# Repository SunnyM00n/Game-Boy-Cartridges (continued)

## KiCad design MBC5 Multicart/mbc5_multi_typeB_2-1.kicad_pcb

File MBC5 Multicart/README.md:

# Game Boy MBC5 Multicart

This is a slightly updated design of my original flashable MBC5-based multicart for the Game Boy. You can make a 2-in-1 or 4-in-1 cartridge, that changes games based on a button press or power cycling the Game Boy. With this board you can also make a single game, but with the addition of a pressable reset button on the cartridge.

**This MBC5 cartridge uses new old stock 29F033 EEPROM chips and battery-backed SRAM.**

The features are as follows:

- Able to make a cartridge with either 2x 2 MB games or 4x 1 MB games
- Adds a pressable button to the cartridge (no shell cutting required)
  - The button can be configured to cycle games on the cart, reset the console, or both
- Configurable to have separate save data for each game, or to share the same save data across multiple games
- Fully compatible with the <a href="https://www.gbxcart.com/">GBxCart RW</a> so you can transfer games and save files to and from the board

Some examples of fun cartridges you can make with this board are:
- A single Pokemon game that has a reset button
- Both Pokemon Red and Blue with separate saves
- Both Pokemon Red and Blue with *the same* save (save files are compatible between versions!)
- Both Pokemon Red and Blue with *the same* save that can switch between versions *during gameplay without resetting* (hotswap!)
- A single copy of Powerpuff Girls with two separate save files

All gerbers and source files can be found in this repo, as this project is fully open source.

## Tutorial Video

This is a video tutorial for the MBC3 multicart specifically, but the process is nearly identical.

")

## Important Things Before You Start

1) To use this board, you need to have an original Game Boy game that uses an MBC5 mapper chip. <a href="https://catskull.net/gb-rom-database/">You can find a list of games and their mappers here</a>. Use the search function. Please note the RAM is in bytes, not bits. Since SRAM in this repo is defined in bits, you need to convert by multiplying the number of bytes by 8.
2) You will need to remove the MBC5 from your donor cartridge for use on this board. This will require a hot air rework station or a hot plate. There's a list below of other parts you can re-use from the donor cartridge.
3) When soldering parts on, it's a good idea to put kapton tape or otherwise cover the bottom cartridge edge. You do not want to get solder on the cartridge contacts.
4) I am not responsible for any damage you do to your self or your property. Attempt this project at your own risk.
5) I do not guarantee design compatibility. You may encounter issues with certain games. There is also a chance I have made an error in the design or the BOM - if this is the case, I will do everything I can to address the problem as quickly as possible.
6) If you are using this board to make games other than for personal use, you must have permission from the originator to use and distribute any ROM images or other related material. You are responsible for making sure you adhere to any license requirements.

DO NOT use my circuit boards for profiting from stolen work - this especially includes homebrew content, ROM hacks, and using fan-made labels without permission from the originator. **Support original creators!**

## Board Characteristics and Order Information

The zipped folder contains all the gerber files for this board. The following options **must** be chosen when ordering boards for yourself.

- Thickness: 0.8mm
- Surface Finish: ENIG
- Gold Fingers: Yes, 30° chamfer

**I sell this blank circuit board on Etsy, so you don't have to buy a bunch of multiples if you don't want to.** (Click the banner!)

You can use the zipped folder at any board fabricator you like. You may also buy the board from PCBWay using this link (disclosure: I receive 10% of the sale value to go twoards future PCB orders of my own):

<a href="https://oshpark.com/shared_projects/IAKoKwEI">The board is also listed on OSH Park as well.</a> **Be sure to get them in 0.8mm thickness if you order from here.**

## Required Equipment

The EEPROM on the board needs to be programmed somehow. There are a few options for doing this:

1) <a href="https://www.gbxcart.com/">**GBxCart**</a>. This is a perfect option if you want an easy way to make Game Boy cartridges without a lot of extra effort. This is a standalone flasher that plugs into your computer via USB. The cartridge circuit board is fully compatible with it, and it makes reflashing games extremely easy using <a href="https://github.com/lesserkuma/FlashGBX">lesserkuma's FlashGBX software</a>.
2) At the lowest level, you can buy an EEPROM programmer with a TSOP chip programming adapter. The downside to this method is that you have to desolder the chip every time you want to program it. The <a href="https://flashcatusb.com/">FlashcatUSB</a> is one popular option in retro spaces, but I use the <a href="https://xgecu.myshopify.com/products/xgecu-new-t48-tl866-3gprogrammer-v12-01-support-28000-ics-for-spi-nor-nand-flash-emmc-bga153-162-169-100-221-tsop-sop-plcc">T48 programmer</a> with the <a href="https://xgecu.myshopify.com/products/100-original-xgecu-adp_f48_ex-1-tsop48-special-adapter-for-nor-flash-only-use-on-t48-tl866-3g-programmer">TSOP48 adapter</a>.

You may also be able to use the <a href="https://github.com/sanni/cartreader">**OSCR**</a> by sanni, but in order to do that you will need to prepare a single ROM file with both games and program it to the first game slot. Or, you will need to add a programming routine into the Arduino code to write a file without erasing the chip first. Consider yourself on your own for this until an addition to the OSCR repository is made to address this.

### How to Program the Cartridges

When using the GBxCart to program multiple games to the cartridge, it's recommended to turn SW2A and SW2B (detailed below) to the OFF position. To change ROM/RAM banks to program, simply press the SW1 tactile button between programming steps. Using FlashGBX's "Refresh" button should show that the game information on the left of the screen changes after pressing the button.

If you're programming the flash chip separate from the board, you'll need to concatenate all the ROM files together into one large 4 MB file to program the chip with.

<a href="https://github.com/MouseBiteLabs/Game-Boy-Cartridges/wiki">Also, you can check out the wiki for more information.</a>

## Battery Safety

When assembling a board, I recommend populating all the parts *except* the battery, and getting it to run initially without it. This is to make it easier to fix any solder connections that might need fixing, without having to worry about getting the battery hot. And if you need to rework anything near the battery after you've put it on the board, be safe and remove it before putting a hot soldering iron next to it.

And this should go without saying, but if you're assembling these boards with a hot plate or hot air, *do not* solder the battery on this way. You should use an iron, and keep heat off of the battery as much as possible. 

(Also check polarity!)

## Board Configurations

There's a lot to cover here. There are four separate switches to configure, and two different sizes of SRAM to pick from.

*Note that you can simply solder bridges from the middle pads of the switches to the left or right to the "ON" or "OFF" positions, instead of installing an actual switch.*

### SRAM Size Selection

There are two sizes of SRAM you can use, and the type you use will dictate how your save data is stored on the cartridge and if it's shared between games or not.

- If you use a 1 Mbit SRAM (like the AS6C1008), then each game you put on the cartridge will have its own separate save files. If you program multiple copies of the same game, then you can effectively have multiple save files on the same cart. Easy example is Pokemon games - they only let you have one save file, but if you put Pokemon Red on the multicart four times, then that gives you four separate save files!
- If you use a 256 Kbit SRAM (like the AS6C62256) then all the games you put on the cartridge will *share* the same RAM space.  This feature is probably only useful for Pokemon games. As an example: this means that if you made a cart that has Pokemon Red and Blue on it, you would play both versions with the same save data, as save data between the two games are compatible with each other.

### Game Cycling Mode Switch (SW2)

SW2, split into two separate switches SW2A (top half) and SW2B (bottom half), controls how you change games on the cartridge. The following table describes the different settings:

| Mode | SW2A (Bottom) | SW2B (Top) | Game change with reset? | Game change with button press? | Does the button reset? |
| ---- | ------------- | ---------- | ----------------------- | ------------------------------ | ---------------------- |
| 1    | OFF           | OFF        | No                      | Yes                            | Yes                    |
| 2    | OFF           | ON         | No                      | Yes                            | No                     |
| 3    | ON            | OFF        | Yes                     | Yes                            | Yes                    |
| 4    | ON            | ON         | Yes                     | No                             | No                     |

*Note: Mode 4 does not give function to the push button at all.*

The "game change" method in this table describes how you advance down the "game" columns described in the table for SW3.

### Game and Save Data Configuration Switch (SW3)

SW3, split into two separate switches SW3A (bottom half) and SW3B (top half), controls the order in which the ROM banks (the games) and the RAM banks (the save data) cycle. This table assumes you are using a 1 Mbit SRAM chip. If you are using a 256 Kbit SRAM, then every entry in the "RAM Banks" column can be described as "1x 256 Kbit", and all the "Game" columns will share that single RAM bank.

Please note that SW3A and SW3B are *different* than the SW3A and SW3B on the MBC3 Multicart PCB.

| Mode | SW3A (Top) | SW3B (Bottom) | ROM Banks  | RAM Banks   | Game 1     | Game 2     | Game 3     | Game 4     |
| ---- | ---- | ---- | ---------- | ----------- | ---------- | ---------- | ---------- | ---------- |
| A    | ON   | OFF  | 2x 2 MB    | 4x 256 Kbit | ROM1, RAM1 | ROM1, RAM2 | ROM2, RAM3 | ROM2, RAM4 |
| B    | OFF  | OFF  | 4x 1 MB    | 4x 256 Kbit | ROM1, RAM1 | ROM2, RAM2 | ROM3, RAM3 | ROM4, RAM4 |
| C    | ON   | ON   | 2x 2 MB    | 2x 256 Kbit | ROM1, RAM1 | ROM2, RAM2 |            |            |
| D    | OFF  | ON   | 2x 1 MB    | 2x 256 Kbit | ROM1, RAM1 | ROM2, RAM2 |            |            |

*Note: Mode D is the same as Mode C, but with restricted space for the ROM, so there's no practical use for Mode D.*

### Game Mode Examples

Here's a list of example cartridges you can make with these settings:
1) Pokemon Red, Blue, Yellow, and Green on one cartridge with separate save files that changes only via pressing the button, which also resets the game: **Mode 1B** with 1 Mbit SRAM
2) Pokemon Red and Blue with separate save files that changes by pressing the button *or* cycling power on the Game Boy: **Mode 3C** with 1 Mbit SRAM
3) Pokemon Red and Blue with the same save file that hotswaps when you press the button on the cartridge (changing games during gameplay): **Mode 2C** with 256 Kbit SRAM

## Test Points and Final Checkout

On the back of the board are five test points. Here's where they are connected:

- TP1: SRAM supply voltage
- TP2: Battery voltage (after R1)
- TP3: Battery voltage (positive terminal of battery)
- TP4: Ground
- TP5: VCC input voltage

After you assemble your game, you should measure the current out of the battery. But first, you should program it with the GBxCart, or if you programmed the EEPROM separately, put it into a Game Boy and cycle power once. Then, flip the PCB upside down on a non-conductive surface (not your leg), and set your multimeter in DC millivolts (or volts). Put the positive probe on TP3 and the negative probe on TP2. If you used a 10kΩ for R1, as indicated in the BOM, you should read a voltage in the single or tens of millivolts. If you have something much higher, especially voltages above 100mV, then you likely have an issue or short circuit on the board somewhere.

**Note: You need to power up the game at least once before battery currents will make sense - the battery management ICs can start up in an unknown state before applying main power to the board.**

To estimate battery life, see <a href="https://github.com/MouseBiteLabs/Game-Boy-MBC5-Cartridge/tree/main/Technical#estimating-battery-life">this section in the Technical Design Document of my first MBC5 design</a>, or for more in-depth analysis, <a href="https://hackaday.io/project/11864-tritiled/log/72554-determining-maximum-runtime-176-to-202-years-cr2032">this Hackaday post</a>.

### Battery Size Considerations

The coin cells commonly used on Game Boy carts in order of increasing size are CR2016, CR2025, and CR2032. The CR2032 is the thickest, but yields the longest battery life.

Batteries that are as large as CR2032 will fit inside the shell, *however*, due to the thickness of the CR2032, using one makes it so the shell cannot be pressed down very easily. This makes the button inside the shell difficult to press reliably. For this reason, I recommend using the CR2025. If you want to use a CR2032 for a bit longer battery life, you should only expect to make a cart that changes games via power cycling only (Modes 3 or 4).

I haven't tested it, but I believe using battery holders instead of pre-tabbed batteries will similarly cause issues with trying to press the button in the middle of the cartridge.

## Board Fitment

The shape of this board was originally meant to mimic original Game Boy circuit boards as closely as possible. Unfortunately, when placed in some aftermarket Game Boy cartridge shells (like those from Cloud Game Store), the circuit board has a lot of freedom to rotate around the main screw hole in the bottom-middle of the cartridge. This can cause misalignment when you put it in a Game Boy, which can cause a game to either not load properly (garbled Game Boy logo) or shut off the Game Boy because of a short circuit. This isn't *dangerous* or anything, just annoying.

In order to make the boards fit nicer in any kind of shell, I added extended tabs of circuit board material to the edges of the cartridges to keep it from rotating too much in shells, which was suggested to me by <a href="https://github.com/orangeglo">orangeglo</a>! (Thanks!)

If you're having trouble fitting the circuit board into a shell, because the tabs interfere with the cart edges, you can safely sand or trim them down as there is no copper within the tabs themselves. The only shell that appears to require any kind of trimming are Kitsch-Bent shells.

## Bill of Materials (BOM)

| Reference Designators | Value/Part Number      | Package        | Description        | Source                                           |
| --------------------- | ---------------------- | -------------- | ------------------ | ------------------------------------------------ |
| B1                    | CR2025, CR2016, CR2032*| See note above | Backup Battery     | [https://mou.sr/3PLccol](https://mou.sr/3PLccol) |
| C1                    | 0.1uF                  | 0603           | Capacitor (MLCC)   | [https://mou.sr/3ENc15O](https://mou.sr/3ENc15O) |
| C4                    | 0.1uF                  | 0603           | Capacitor (MLCC)   | [https://mou.sr/3ENc15O](https://mou.sr/3ENc15O) |
| C5                    | 0.1uF                  | 0603           | Capacitor (MLCC)   | [https://mou.sr/3ENc15O](https://mou.sr/3ENc15O) |
| C6                    | 10uF                   | 0603           | Capacitor (MLCC)   | [https://mou.sr/3mZtSkF](https://mou.sr/3mZtSkF) |
| C7                    | 0.1uF                  | 0603           | Capacitor (MLCC)   | [https://mou.sr/3ENc15O](https://mou.sr/3ENc15O) |
| C8                    | 0.01uF                 | 0603           | Capacitor (MLCC)   | [https://mou.sr/3AsRwK1](https://mou.sr/3AsRwK1) |
| C12                   | 0.1uF                  | 0603           | Capacitor (MLCC)   | [https://mou.sr/3ENc15O](https://mou.sr/3ENc15O) |
| Q1                    | 2N7002                 | SOT-23         | N-Channel FET      | [https://mou.sr/3rgfh6J](https://mou.sr/3rgfh6J) |
| R1                    | 10k                    | 0603           | Resistor           | [https://mou.sr/3riR7IH](https://mou.sr/3riR7IH) |
| R5                    | 130k                   | 0603           | Resistor           | [https://mou.sr/3MjXliy](https://mou.sr/3MjXliy) |
| R6                    | 130k                   | 0603           | Resistor           | [https://mou.sr/3MjXliy](https://mou.sr/3MjXliy) |
| R9                    | 130k                   | 0603           | Resistor           | [https://mou.sr/3MjXliy](https://mou.sr/3MjXliy) |
| R10                   | 49.9k                  | 0603           | Resistor           | [https://mou.sr/3Q3NRZO](https://mou.sr/3Q3NRZO) |
| SW1                   | See note               | 5.2 x 5.2mm    | Tactile Switch     | See Note |
| SW2                   | CAS-D20TA              | J Form Lead    | Dual SPDT          | [https://mou.sr/44YZNT5](https://mou.sr/44YZNT5) |
| SW3                   | CAS-D20TA              | J Form Lead    | Dual SPDT          | [https://mou.sr/44YZNT5](https://mou.sr/44YZNT5) |
| U1                    | 29F032, 29F033         | TSOP-40        | Flash EEPROM       | AliExpress or eBay                               |
| U2                    | MBC5                   | QFP-32         | MBC5 Mapper        | Donor MBC5 Game Boy cartridge                    |
| U3                    | AS6C62256, AS6C1008    | SOP-28, SOP-32 | SRAM               | [https://mou.sr/3sFegFF](https://mou.sr/3sFegFF) |
| U4                    | TPS3613                | MSOP-10        | Battery Management | [https://mou.sr/45Ir2kh](https://mou.sr/45Ir2kh) |
| U5                    | SN74HCS74              | TSSOP-14       | Dual Flip Flop     | [https://mou.sr/3QYGEuT](https://mou.sr/3QYGEuT) |
| U6                    | SN74AHC1G126           | SC70           | Tri-State Buffer   | [https://mou.sr/3T9Zdim](https://mou.sr/3T9Zdim) |
| U7                    | SN74AHC1G126           | SC70           | Tri-State Buffer   | [https://mou.sr/3T9Zdim](https://mou.sr/3T9Zdim) |
| U8                    | SN74AHC1G126           | SC70           | Tri-State Buffer   | [https://mou.sr/3T9Zdim](https://mou.sr/3T9Zdim) |

### Note about SW1

If SW1 is long enough, it will sit inside the shell in a way that lets you press it by lightly pressing on the cartridge shell. This way, you can activate it without removing it from the console. You need to find a switch that has an extended stem on AliExpress, eBay, or Amazon (**if you find a compatible switch on Mouser or Digikey, please let me know**). The measurements will be 5.2 mm x 5.2 mm, with a height of 3.5 mm. Sometimes these parts are listed as "4 mm x 4 mm" or "5 mm x 5 mm" instead. Check the datasheet, if available, to see if it'll fit the footprint. They should have listing pictures similar to the ones seen here:

### Note about SW2, SW3

Instead of using the somewhat pricey switch designated for SW2 and SW3, you can instead just bridge the pads with solder from the middle pad to the pad in the direction you want to set the switch to. For example - in the below picture, SW3A and SW3B are both in the "ON" position in both cases. (Note that the white switches on the right image are switched to the right.)

### Usable Donor Cartridge Parts

You can use a few parts from the donor cart on the new board to save some money. Note that you will generally get better reliability with new parts as opposed to old ones. For example: I have seen failed RAM chips from donors in the past.

1) **U2: MBC5** - This one is required
2) **U3: SRAM** - You can use this part *only if* the sum of the RAM space for the games you're using is the same or less amount of RAM that the donor cartridge has. If you plan to have separate save data for every game, you'll probably need to buy an AS6C1008.

You could probably transfer over most of the 0.1uF capacitors but they're pretty cheap anyway, so I generally just recommend buying new resistors and capacitors.

## Things to Remember

- The 29F032 and 29F033 have been known to occasionally be defective upon arrival. They're either used, or new old stock, and usually only available from AliExpress.
- The footprint for the battery can fit a CR2032, CR2025, or CR2016 with solder tabs. The only difference is the mAh capacity (larger number = longer life). If you get Panasonic tabbed batteries, you may have to trim the battery tabs to make them fit on the footprint.
- Generally, ROM sizes are conveyed in terms of kilobytes and megabytes (KB, MB). RAM size is usually conveyed in terms of kilobits or megabits (Kbit, Mbit). You can convert Kbit and Mbit to KB and MB by dividing Kbit or Mbit by 8. For example, 256 Kbit = 32 KB.

## Labels

If you want a Bucket Mouse branded label for your cartridge, look no further than <a href="https://krizdingus.com/mousebitelabs/">krizdingus's designs</a>. Special thanks to Kris for designing these, they look awesome! (If you are going to order/print these, use the high-res images hosted on his website, and *keep the labels for personal or non-commercial use only.*)

## Why not FRAM?

This particular board is designed for using low retention power SRAM, or Static RAM. One downside to SRAM is that you need a battery to keep the SRAM powered on even when the game is turned off if you want to retain the data on the chip. So eventually the battery will die, and your save data will be lost.

The other popular option for holding save data is using FRAM, or Ferroelectric RAM, to keep save data around even after the battery dies (specifically, the popular part that's used for Game Boy FRAM carts is the FM18W08).

So, why would anyone ever use SRAM over FRAM if FRAM doesn't need a battery? Well, they do come with a number of downsides:

1) Quality, new stock, 5V tolerant FRAM is expensive ($12+ per part).
2) Cheaper FRAM chips from eBay or Aliexpress are notoriously flaky (anecdotally, ~50% success rate).
3) **FM18W08 maxes out at 256K (which is restrictive for multicarts).**
4) FRAM memory access requires different chip select timing than SRAM, and the Game Boy expects SRAM, so it is not natively compatible with FRAM carts. The Gameboy Color specifically cannot (easily) be made to properly access FM18W08 chip. You *can* use an OR gate and add the CLK on the cart edge to try to achieve the necessary timing, but it only works (properly) for DMG/MGB/SGB, not the GBC. It usually *works* in practice for GBC, but it's technically a datasheet violation and can potentially cause issues in edge cases. <a href="https://github.com/Gekkio">(Thanks to gekkio for pointing this out!)</a>

In contrast, *brand new* quality SRAM chips are ~$3, and you can even save that by using the original SRAM from a donor cartridge if you want to. You will easily get more than a decade of life running on a battery. You're already assembling this cartridge; you can dump the save and replace the battery before then.

## Revision History

### v2.1
- Removed triangle on silkscreen from U8

### v2.0
- Fixed issue with previous design where SW2A being in the ON position caused excess save battery drain
- Added board number to the top of the board
- Updated silkscreen and cartridge style to match my other Game Boy cartridges
- Removed R8, made EEPROM writable via the /WR pin on the cart edge

### v1.3
- Fixed debounce circuit for push button
- Adjusted board edge tabs to better fit in shells

### v1.2
- Added nubs on the board edge to prevent the circuit board from rattling around in aftermarket cartridges

### v1.1
- Fix schematic errors
- Extended cart edge down by 0.25 mm for better fitment
- Added OSHW logo and "SUPPORT ORIGINAL CREATORS!"

### v1.0
- Prototype revision

## Resources and Acknowledgements

- <a href="http://www.devrs.com/gb/files/hardware.html">Jeff Frohwein's GameBoy Tech Page</a>
- <a href="https://gbhwdb.gekkio.fi/">Game Boy Hardware Database</a>
- <a href="https://catskull.net/gb-rom-database/">Nintendo Gameboy Game List</a>
- <a href="https://www.gbxcart.com/">insideGadgets discord server for GBxCart RW compatibility requirements</a>
- <a href="https://github.com/lesserkuma/FlashGBX">Lesserkuma's FlashGBX software</a>
- <a href="https://www.ti.com/lit/ds/symlink/tps3613-01.pdf?HQS=dis-mous-null-mousermode-dsf-pf-null-wwe&ts=1698238885366&ref_url=https%253A%252F%252Feu.mouser.com%252F">TPS3613 Datasheet</a>
- Board outline modified from <a href="https://tinkerer.us/projects/homebrew-gameboy-cartridge.html">Dillon Nichols's Homebrew Gameboy Cartridge project</a>
- Thanks to <a href="https://github.com/orangeglo">orangeglo</a> for his suggestion of adding spacers around the board edge for better fitment in aftermarket cartridges
- Some components from <a href="https://github.com/adafruit/Adafruit-Eagle-Library">Adafruit's Eagle parts library</a>
- Some components from <a href="https://www.snapeda.com/">SnapMagic</a>
- Thank you to <a href="https://github.com/Gekkio">gekkio</a> for their deep Game Boy knowledge resources, and for collaboration in demystifying some of the design choices on Game Boy cartridges

## License

<br />This work is licensed under a <a rel="license" href="http://creativecommons.org/licenses/by-sa/4.0/">Creative Commons Attribution-ShareAlike 4.0 International License</a>. You are able to copy and redistribute the material in any medium or format, as well as remix, transform, or build upon the material for any purpose (even commercial) - but you **must** give appropriate credit, provide a link to the license, and indicate if any changes were made.

©MouseBiteLabs 2025

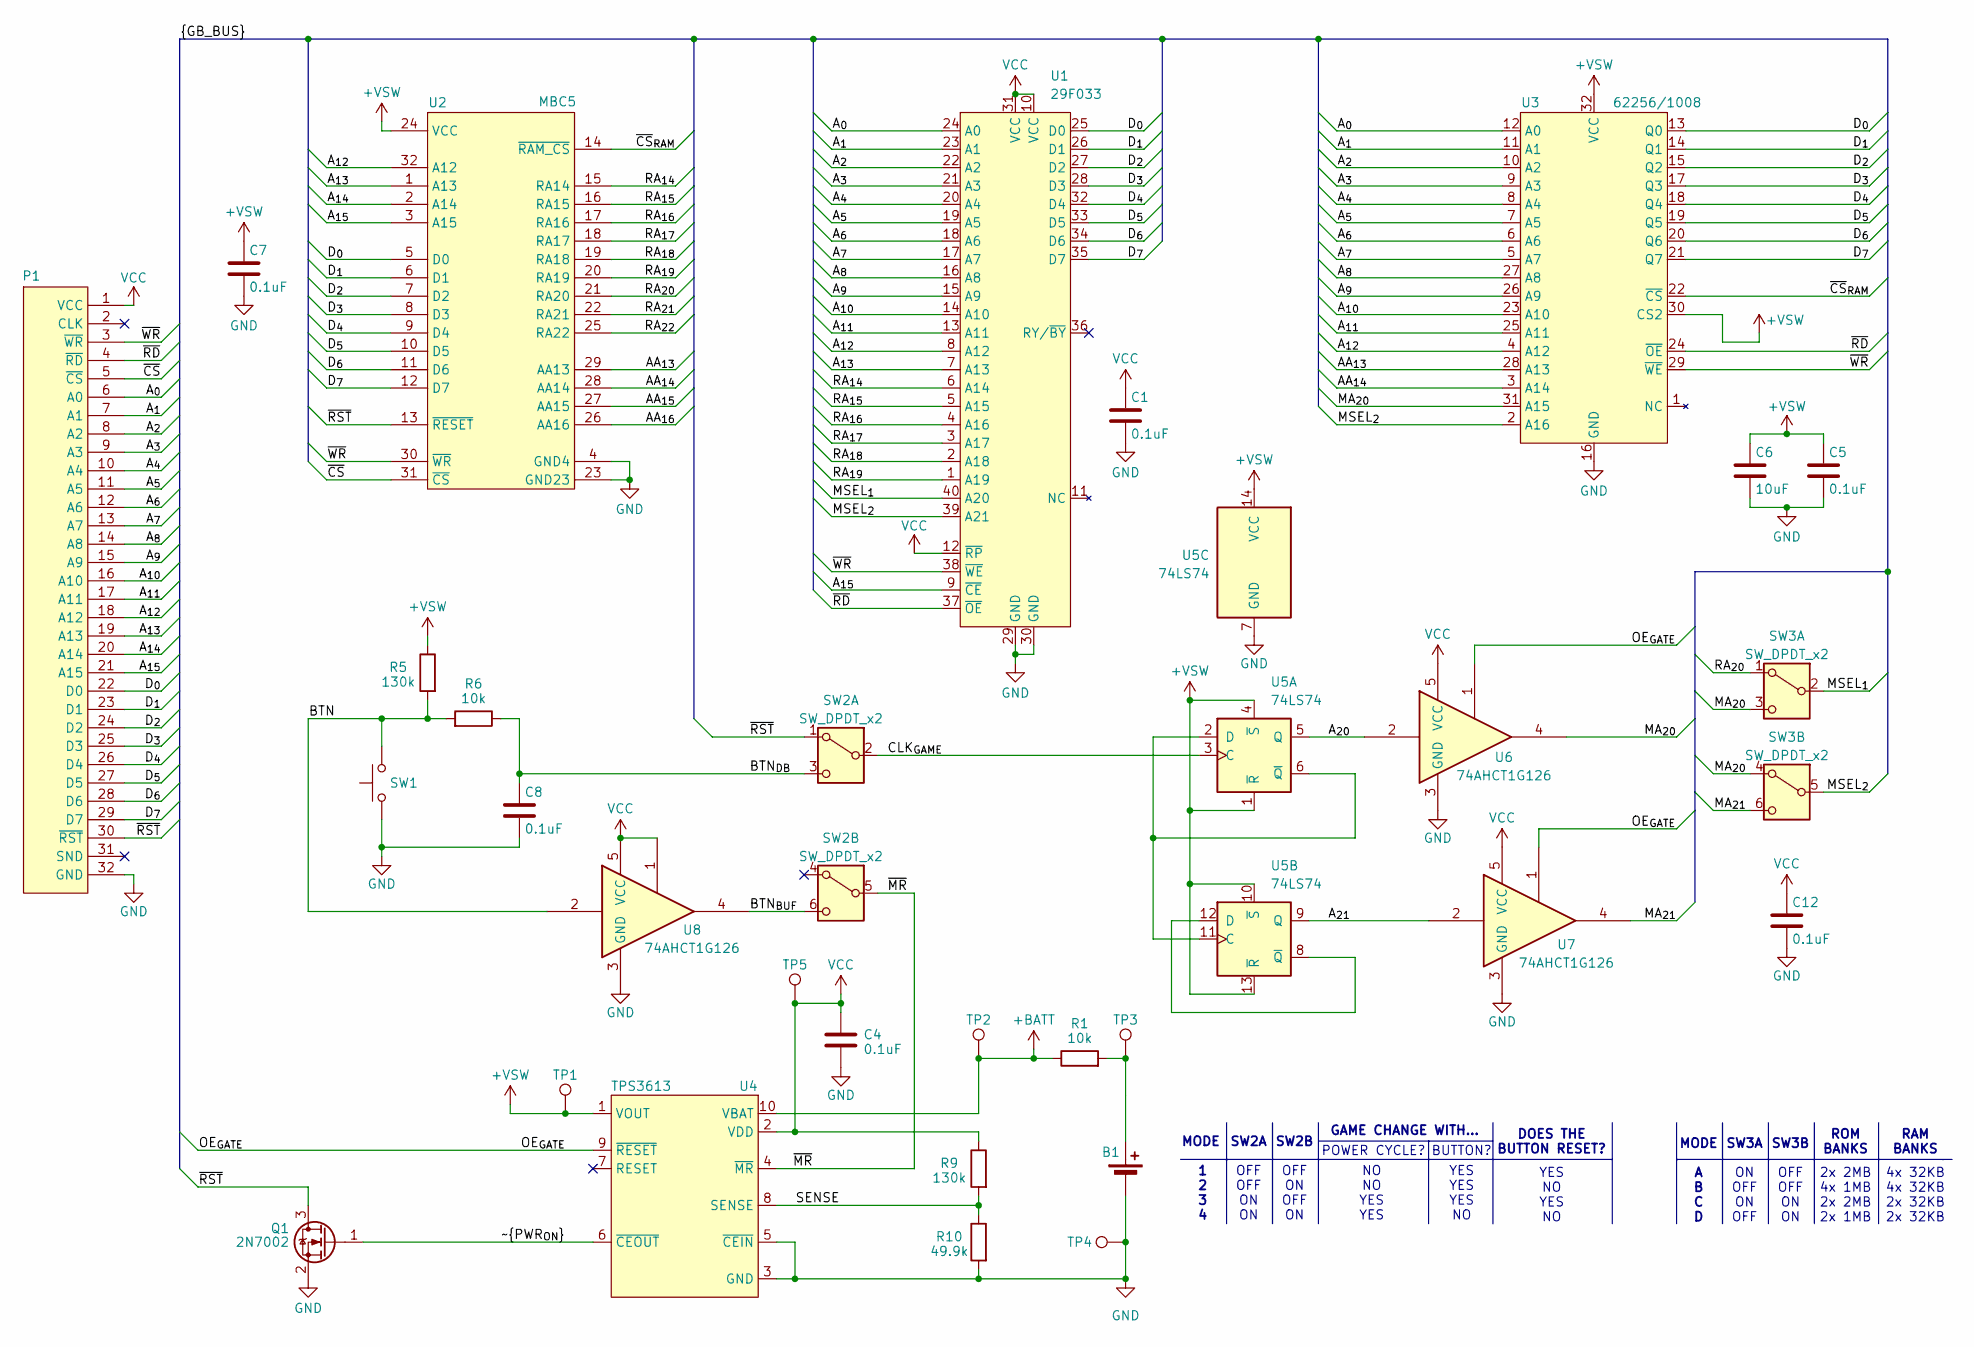
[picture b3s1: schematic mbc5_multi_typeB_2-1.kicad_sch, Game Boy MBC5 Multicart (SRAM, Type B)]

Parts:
B1: CR2025
C1, C4, C5, C7, C8, C12: 0.1uF; C_0603_1608Metric_Boxed
C6: 10uF; C_0603_1608Metric_Boxed
P1: GBC_CARTTAB; GBC_CART_TABBED
Q1: 2N7002; SOT-23
R1, R6: 10k; R_0603_1608Metric_Boxed
R5, R9: 130k; R_0603_1608Metric_Boxed
R10: 49.9k; R_0603_1608Metric_Boxed
SW1: SW_SPST_Momentary; Pushbutton
SW2, SW3: SW_DPDT_x2; CAS-D20A
TP1, TP2, TP3, TP4, TP5: TPB1,27; TestPoint_Pad_D1.0mm
U1: 29F033; TSOP-I-40_18.4x12mm_P0.5mm_1
U2: MBC5; QFP-32
U3: 62256/1008; SO32L_L
U4: TPS3613; MSOP-10_3x3mm_P0.5mm
U5: 74LS74; TSSOP-14_4.4x5mm_P0.65mm
U6, U7, U8: 74AHCT1G126; SOT-353_SC-70-5

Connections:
+BATT: R1.1, TP2.1, U4.10 (VBAT)
+VSW: C5.1, C6.1, C7.1, R5.1, TP1.1, U2.24 (VCC), U3.30 (CS2), U3.32 (VCC), U4.1 (VOUT), U5.1 (~R), U5.4 (~S), U5.10 (~S), U5.13 (~R), U5.14 (VCC)
/AA_{13}: U2.29 (AA13), U3.28 (A13)
/AA_{14}: U2.28 (AA14), U3.3 (A14)
/AA_{15}: U2.27 (AA15)
/AA_{16}: U2.26 (AA16)
/A_{0}: P1.6 (A0), U1.24 (A0), U3.12 (A0)
/A_{1}: P1.7 (A1), U1.23 (A1), U3.11 (A1)
/A_{2}: P1.8 (A2), U1.22 (A2), U3.10 (A2)
/A_{3}: P1.9 (A3), U1.21 (A3), U3.9 (A3)
/A_{4}: P1.10 (A4), U1.20 (A4), U3.8 (A4)
/A_{5}: P1.11 (A5), U1.19 (A5), U3.7 (A5)
/A_{6}: P1.12 (A6), U1.18 (A6), U3.6 (A6)
/A_{7}: P1.13 (A7), U1.17 (A7), U3.5 (A7)
/A_{8}: P1.14 (A8), U1.16 (A8), U3.27 (A8)
/A_{9}: P1.15 (A9), U1.15 (A9), U3.26 (A9)
/A_{10}: P1.16 (A10), U1.14 (A10), U3.23 (A10)
/A_{11}: P1.17 (A11), U1.13 (A11), U3.25 (A11)
/A_{12}: P1.18 (A12), U1.8 (A12), U2.32 (A12), U3.4 (A12)
/A_{13}: P1.19 (A13), U1.7 (A13), U2.1 (A13)
/A_{14}: P1.20 (A14), U2.2 (A14)
/A_{15}: P1.21 (A15), U1.9 (~CE), U2.3 (A15)
/A_{20}: U5.5 (Q), U6.2
/A_{21}: U5.9 (Q), U7.2
/BTN: R5.2, R6.2, SW1.2, U8.2
/BTN_{BUF}: SW2.6 (C), U8.4
/BTN_{DB}: C8.1, R6.1, SW2.3 (C)
/CLK_{GAME}: SW2.2 (B), U5.3 (C)
/D_{0}: P1.22 (D0), U1.25 (D0), U2.5 (D0), U3.13 (Q0)
/D_{1}: P1.23 (D1), U1.26 (D1), U2.6 (D1), U3.14 (Q1)
/D_{2}: P1.24 (D2), U1.27 (D2), U2.7 (D2), U3.15 (Q2)
/D_{3}: P1.25 (D3), U1.28 (D3), U2.8 (D3), U3.17 (Q3)
/D_{4}: P1.26 (D4), U1.32 (D4), U2.9 (D4), U3.18 (Q4)
/D_{5}: P1.27 (D5), U1.33 (D5), U2.10 (D5), U3.19 (Q5)
/D_{6}: P1.28 (D6), U1.34 (D6), U2.11 (D6), U3.20 (Q6)
/D_{7}: P1.29 (D7), U1.35 (D7), U2.12 (D7), U3.21 (Q7)
/MA_{20}: SW3.3 (C), SW3.4 (A), U3.31 (A15), U6.4
/MA_{21}: SW3.6 (C), U7.4
/MSEL_{1}: SW3.2 (B), U1.40 (A20)
/MSEL_{2}: SW3.5 (B), U1.39 (A21), U3.2 (A16)
/OE_{GATE}: U4.9 (~RESET), U6.1, U7.1
/RA_{14}: U1.6 (A14), U2.15 (RA14)
/RA_{15}: U1.5 (A15), U2.16 (RA15)
/RA_{16}: U1.4 (A16), U2.17 (RA16)
/RA_{17}: U1.3 (A17), U2.18 (RA17)
/RA_{18}: U1.2 (A18), U2.19 (RA18)
/RA_{19}: U1.1 (A19), U2.20 (RA19)
/RA_{20}: SW3.1 (A), U2.21 (RA20)
/RA_{21}: U2.22 (RA21)
/RA_{22}: U2.25 (RA22)
/SENSE: R9.2, R10.1, U4.8 (SENSE)
/~CS: P1.5 (~CS), U2.31 (~CS)
/~CS_{RAM}: U2.14 (~RAM_CS), U3.22 (~CS)
/~MR: SW2.5 (B), U4.4 (~MR)
/~PWR_{ON}: Q1.1 (G), U4.6 (~CEOUT)
/~RD: P1.4 (~RD), U1.37 (~OE), U3.24 (~OE)
/~RST: P1.30 (~RST), Q1.3 (D), SW2.1 (A), U2.13 (~RESET)
/~WR: P1.3 (~WR), U1.38 (~WE), U2.30 (~WR), U3.29 (~WE)
GND: B1.2 (-), C1.2, C4.2, C5.2, C6.2, C7.2, C8.2, C12.2, P1.32 (GND), Q1.2 (S), R10.2, SW1.1, TP4.1, U1.29 (GND), U1.30 (GND), U2.4 (GND4), U2.23 (GND23), U3.16 (GND), U4.3 (GND), U4.5 (~CEIN), U5.7 (GND), U6.3 (GND), U7.3 (GND), U8.3 (GND)
unnamed: B1.1 (+), R1.2, TP3.1
unnamed: U5.2 (D), U5.6 (~Q), U5.11 (C)
unnamed: U5.8 (~Q), U5.12 (D)
VCC: C1.1, C4.1, C12.1, P1.1 (VCC), R9.1, TP5.1, U1.10 (VCC), U1.12 (~RP), U1.31 (VCC), U4.2 (VDD), U6.5 (VCC), U7.5 (VCC), U8.1, U8.5 (VCC)

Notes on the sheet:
RAM BANKS
BUTTON?
A B C D
YES NO YES NO
SW2A
SW3B
OFF OFF ON ON
MODE
OFF ON OFF ON
DOES THE BUTTON RESET?
YES YES YES NO
1 2 3 4
4x 32KB 4x 32KB 2x 32KB 2x 32KB
ROM BANKS
SW3A
POWER CYCLE?
NO NO YES YES
SW2B
2x 2MB 4x 1MB 2x 2MB 2x 1MB
GAME CHANGE WITH...
ON OFF ON OFF

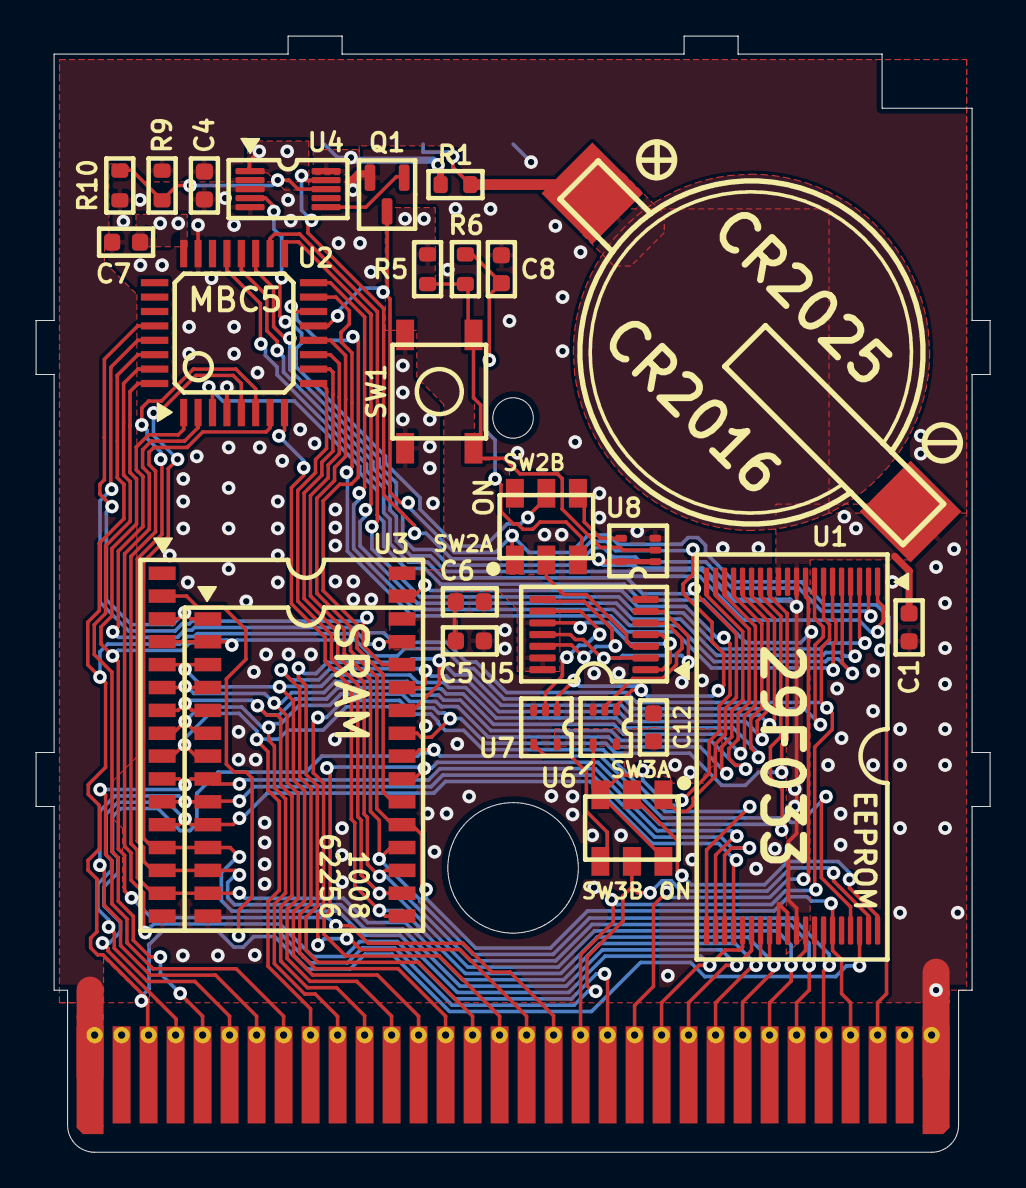
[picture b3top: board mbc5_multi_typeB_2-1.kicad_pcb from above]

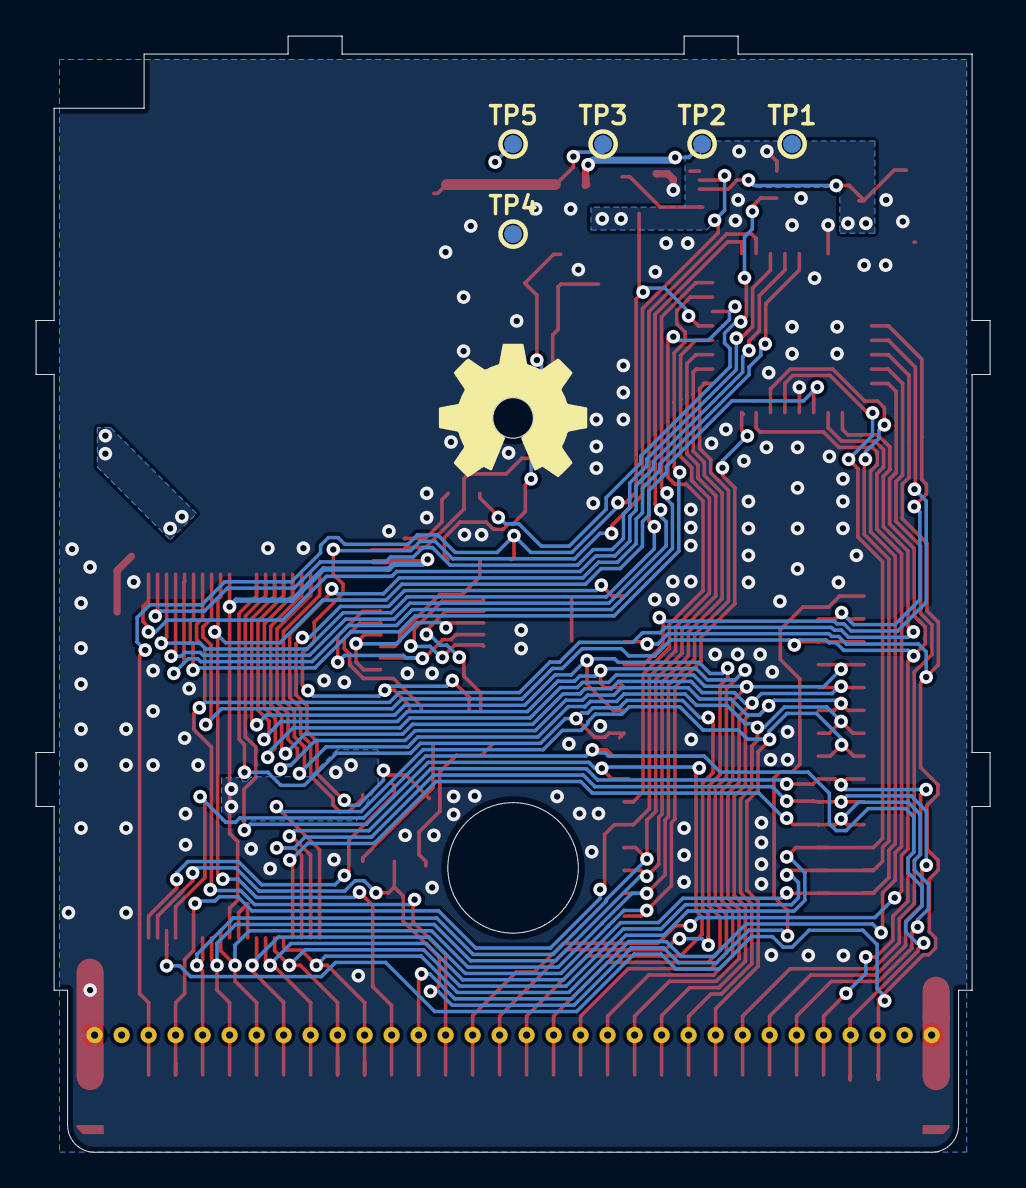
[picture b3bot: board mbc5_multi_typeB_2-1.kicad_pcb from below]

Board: 2 copper layers, 53.0 x 62.0 mm, 31 parts (5 on the bottom side), 59 nets.

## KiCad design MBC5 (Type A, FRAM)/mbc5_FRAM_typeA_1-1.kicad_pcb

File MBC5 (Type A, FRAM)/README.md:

# Game Boy MBC5 Cartridge - Type A, FRAM

This is an alternate design of my <a href="https://github.com/MouseBiteLabs/Game-Boy-Cartridges/tree/main/MBC5%20(Type%20A%2C%20SRAM)">flashable MBC5-based cartridge for the Game Boy</a>. This board uses non-volatile FRAM instead of SRAM to hold save data. I made this specifically for use with the <a href="https://github.com/MouseBiteLabs/Super-Game-Boy-Plus/tree/main">Super Game Boy Plus boards.</a>

**This MBC5 cartridge uses brand new M29F160 EEPROM chips and non-volatile FRAM.**

This circuit board should cover most MBC5 games, and is able to make games up to 2 MB in size, that use up to 256 Kbit of RAM. It is fully compatible with both the <a href="https://www.gbxcart.com/">GBxCart RW</a> and sanni's <a href="https://github.com/sanni/cartreader">Open Source Cart Reader (OSCR)</a> so you can transfer games and save files to and from the board. Because of the FRAM this board utilizes, <a href="https://github.com/MouseBiteLabs/Game-Boy-Cartridges/tree/main/MBC5%20(Type%20A%2C%20SRAM)#why-not-fram">it is technically only fully compatible with regular Game Boy games, and not Game Boy Color games,</a> though no issues have been reported in the past when using them with Game Boy Color games.

All gerbers and source files can be found in this repo, as this project is fully open source.

## Important Things Before You Start

1) To use this board, you need to have an original Game Boy game that uses an MBC5 mapper chip. <a href="https://catskull.net/gb-rom-database/">You can find a list of games and their mappers here</a>. Use the search function. Please note the RAM is in bytes, not bits. Since RAM in this repo is defined in bits, you need to convert by multiplying the number of bytes by 8.
2) You will need to remove the MBC5 from your donor cartridge for use on this board. This will require a hot air rework station or a hot plate. There's a list below of other parts you can re-use from the donor cartridge.
3) When soldering parts on, it's a good idea to put kapton tape or otherwise cover the bottom cartridge edge. You do not want to get solder on the cartridge contacts.
4) I am not responsible for any damage you do to your self or your property. Attempt this project at your own risk.
5) I do not guarantee design compatibility. You may encounter issues with certain games. There is also a chance I have made an error in the design or the BOM - if this is the case, I will do everything I can to address the problem as quickly as possible.
6) If you are using this board to make games other than for personal use, you must have permission from the originator to use and distribute any ROM images or other related material. You are responsible for making sure you adhere to any license requirements.

DO NOT use my circuit boards for profiting from stolen work - this especially includes homebrew content, ROM hacks, and using fan-made labels without permission from the originator. **Support original creators!**

## Board Characteristics and Order Information

The zipped folder contains all the gerber files for this board. The following options **must** be chosen when ordering boards for yourself.

- Thickness: 0.8mm
- Surface Finish: ENIG
- Gold Fingers: Yes, 30° chamfer

**I sell this blank circuit board on Etsy, so you don't have to buy a bunch of multiples if you don't want to.** (Click the banner!)

(Not yet available - this is a placeholder.)

You can use the zipped folder at any board fabricator you like. You may also buy the board from PCBWay using this link (disclosure: I receive 10% of the sale value to go towards future PCB orders of my own):

<a href="https://oshpark.com/shared_projects/4iVMHuUe">The board is also listed on OSH Park as well.</a> **Be sure to get them in 0.8mm thickness if you order from here.**

## Required Equipment

The EEPROM on the board needs to be programmed somehow. There are a few options for doing this:

1) <a href="https://www.gbxcart.com/">**GBxCart**</a>. This is a perfect option if you want an easy way to make Game Boy cartridges without a lot of extra effort. This is a standalone flasher that plugs into your computer via USB. The cartridge circuit board is fully compatible with it, and it makes reflashing games extremely easy using <a href="https://github.com/lesserkuma/FlashGBX">lesserkuma's FlashGBX software</a>.
2) <a href="https://github.com/sanni/cartreader">**OSCR**</a> by sanni. This is the Open Source Cart Reader, capable of making backups of both the ROM and RAM contents of cartridges across many different systems - like the NES, SNES, Genesis, and of course Game Boy and Game Boy Advance. And you can also use it to flash these Game Boy cartridges. The OSCR however requires assembly (or someone to assemble it for you) and is a bit more cumbersome to interface with on a PC, but it's an extremely powerful tool that I can't recommend enough if you want to expand past Game Boys.
3) At the lowest level, you can buy an EEPROM programmer with a TSOP chip programming adapter. The downside to this method is that you have to desolder the chip every time you want to program it. The <a href="https://flashcatusb.com/">FlashcatUSB</a> is one popular option in retro spaces, but I use the <a href="https://xgecu.myshopify.com/products/xgecu-new-t48-tl866-3gprogrammer-v12-01-support-28000-ics-for-spi-nor-nand-flash-emmc-bga153-162-169-100-221-tsop-sop-plcc">T48 programmer</a> with the <a href="https://xgecu.myshopify.com/products/100-original-xgecu-adp_f48_ex-1-tsop48-special-adapter-for-nor-flash-only-use-on-t48-tl866-3g-programmer">TSOP48 adapter</a>.

### How to Program the Cartridges

<a href="https://github.com/MouseBiteLabs/Game-Boy-Cartridges/wiki">Check out the wiki for more information.</a>

## Board Fitment

The shape of this board was originally meant to mimic original Game Boy circuit boards as closely as possible. Unfortunately, when placed in some aftermarket Game Boy cartridge shells (like those from Cloud Game Store), the circuit board has a lot of freedom to rotate around the main screw hole in the bottom-middle of the cartridge. This can cause misalignment when you put it in a Game Boy, which can cause a game to either not load properly (garbled Game Boy logo) or shut off the Game Boy because of a short circuit. This isn't *dangerous* or anything, just annoying.

In order to make the boards fit nicer in any kind of shell, I added extended tabs of circuit board material to the edges of the cartridges to keep it from rotating too much in shells, which was suggested to me by <a href="https://github.com/orangeglo">orangeglo</a>! (Thanks!)

If you're having trouble fitting the circuit board into a shell, because the tabs interfere with the cart edges, you can safely sand or trim them down as there is no copper within the tabs themselves. The only shell that appears to require any kind of trimming are Kitsch-Bent shells.

## Bill of Materials (BOM)

| Reference | Value/Part Number | Package | Description      | Source                                           |
| --------- | ----------------- | ------- | ---------------- | ------------------------------------------------ |
| C19       | 0.1u              | 0603    | Capacitor (MLCC) | [https://mou.sr/3ENc15O](https://mou.sr/3ENc15O) |
| C20       | 0.1u              | 0603    | Capacitor (MLCC) | [https://mou.sr/3ENc15O](https://mou.sr/3ENc15O) |
| C21       | 0.1u              | 0603    | Capacitor (MLCC) | [https://mou.sr/3ENc15O](https://mou.sr/3ENc15O) |
| C22       | 0.1u              | 0603    | Capacitor (MLCC) | [https://mou.sr/3ENc15O](https://mou.sr/3ENc15O) |
| R17       | 10k               | 0603    | Resistor         | [https://mou.sr/3riR7IH](https://mou.sr/3riR7IH) |
| U7        | M29F160           | TSOP-48 | Flash EEPROM     | [https://mou.sr/3MNWQ0b](https://mou.sr/3MNWQ0b) |
| U8        | MBC5              | QFP-32  | MBC5 Mapper      | Donor Game Boy Game                              |
| U9        | FM18W08-SG        | SOIC-28 | FRAM             | [https://mou.sr/4cRIJlb](https://mou.sr/4cRIJlb) |
| U10       | SN74LVC1G332      | SOT-363 | 3-input Or Gate  | [https://mou.sr/3XdbXoN](https://mou.sr/3XdbXoN) |

## Labels

If you want a Bucket Mouse branded label for your cartridge, look no further than <a href="https://krizdingus.com/mousebitelabs/">krizdingus's designs</a>. Special thanks to Kris for designing these, they look awesome! (If you are going to order/print these, use the high-res images hosted on his website, and *keep the labels for personal or non-commercial use only.*)

## Revision History

### v1.1
- Fix board number and update silkscreen for consistency

### v1.0
- Initial revision

## Resources and Acknowledgements

- <a href="http://www.devrs.com/gb/files/hardware.html">Jeff Frohwein's GameBoy Tech Page</a>
- <a href="https://gbhwdb.gekkio.fi/">Game Boy Hardware Database</a>
- <a href="https://catskull.net/gb-rom-database/">Nintendo Gameboy Game List</a>
- <a href="https://www.gbxcart.com/">insideGadgets discord server for GBxCart RW compatibility requirements</a>
- <a href="https://github.com/lesserkuma/FlashGBX">Lesserkuma's FlashGBX software</a>
- <a href="https://github.com/sanni/cartreader">sanni's Open Source Cart Reader (OSCR)</a>, and thanks to the OSCR discord server for help and feedback
- Board outline modified from <a href="https://tinkerer.us/projects/homebrew-gameboy-cartridge.html">Dillon Nichols's Homebrew Gameboy Cartridge project</a>
- Thanks to <a href="https://github.com/orangeglo">orangeglo</a> for his suggestion of adding spacers around the board edge for better fitment in aftermarket cartridges
- Some components from <a href="https://github.com/adafruit/Adafruit-Eagle-Library">Adafruit's Eagle parts library</a>
- Some components from <a href="https://www.snapeda.com/">SnapMagic</a>
- Thank you to <a href="https://github.com/Gekkio">gekkio</a> for their deep Game Boy knowledge resources, and for collaboration in demystifying some of the design choices on Game Boy cartridges

## License

<br />This work is licensed under a <a rel="license" href="http://creativecommons.org/licenses/by-sa/4.0/">Creative Commons Attribution-ShareAlike 4.0 International License</a>. You are able to copy and redistribute the material in any medium or format, as well as remix, transform, or build upon the material for any purpose (even commercial) - but you **must** give appropriate credit, provide a link to the license, and indicate if any changes were made.

©MouseBiteLabs 2025

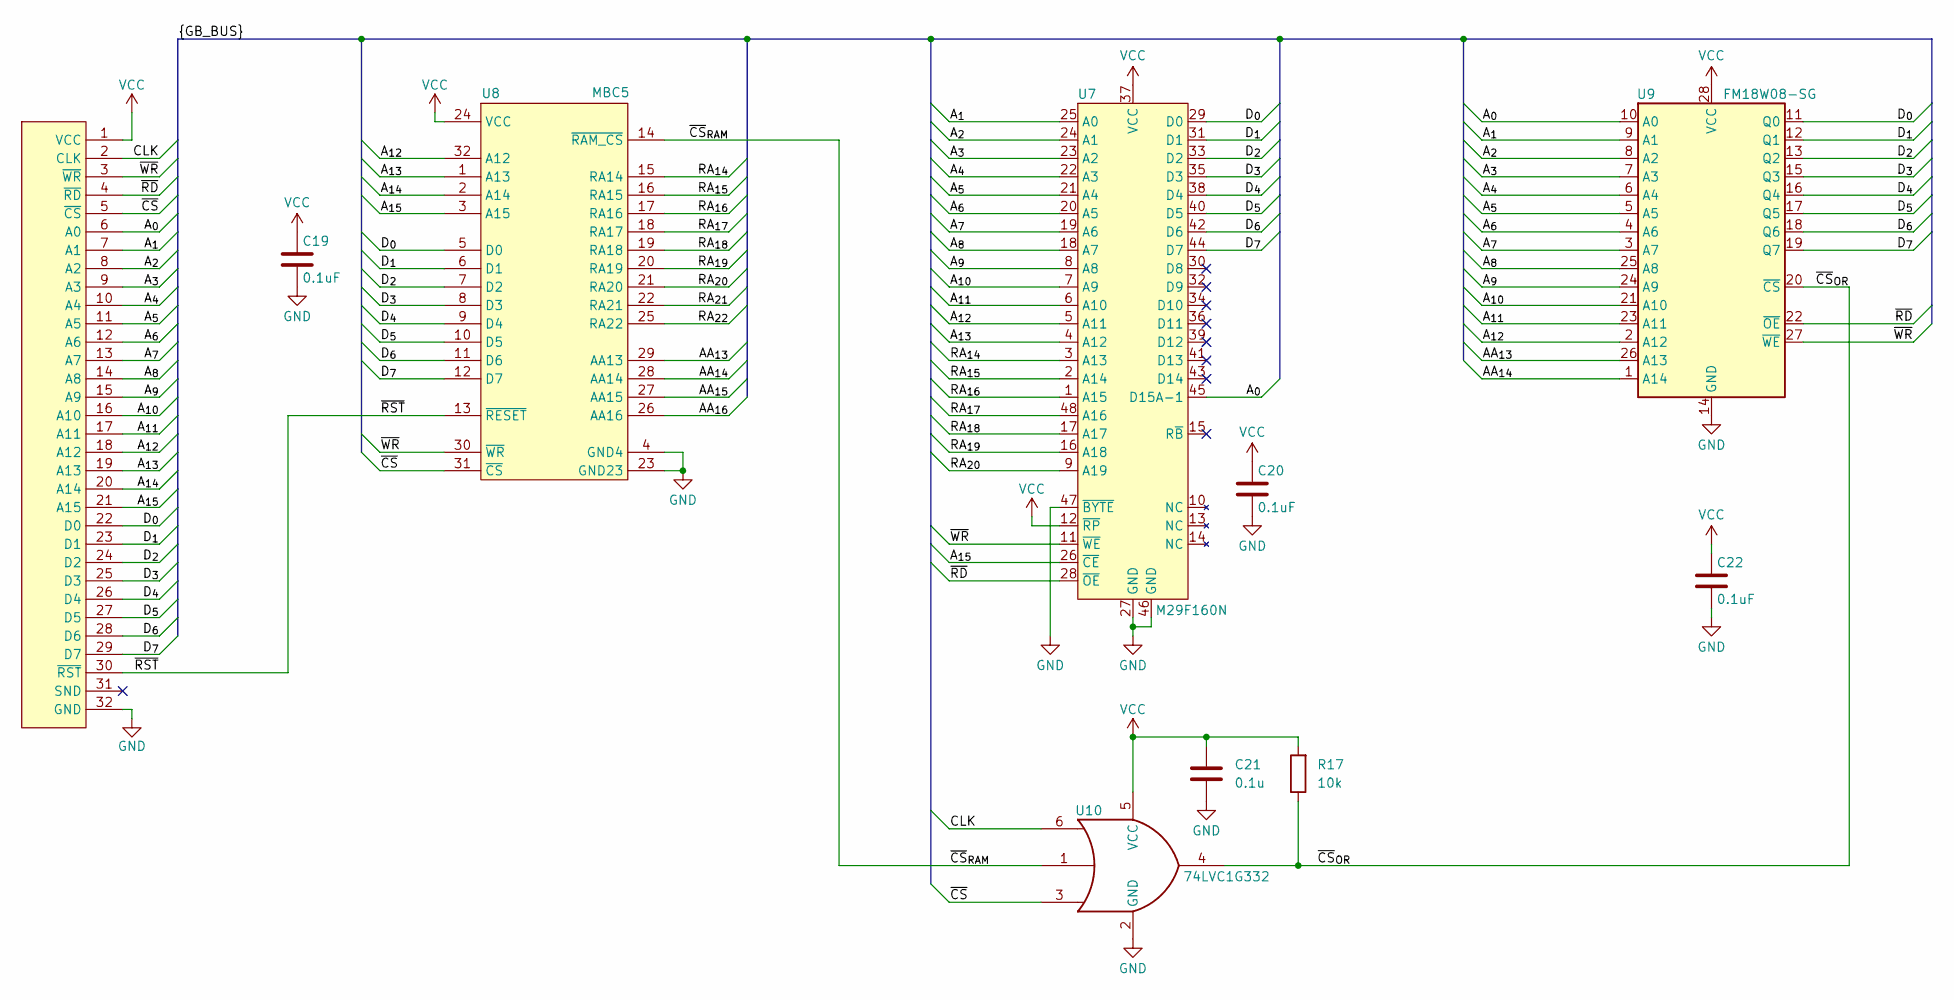
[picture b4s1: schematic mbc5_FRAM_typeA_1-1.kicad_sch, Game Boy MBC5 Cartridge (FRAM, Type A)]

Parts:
C19, C20, C22: 0.1uF; C_0603_1608Metric_Boxed
C21: 0.1u; C_0603_1608Metric_Boxed
P1: GBC_CARTTAB; GBC_CART_TABBED
R17: 10k; R_0603_1608Metric_Boxed
U7: M29F160N; TSOP-I-48_18.4x12mm_P0.5mm
U8: MBC5; QFP-32
U9: FM18W08-SG; SO28
U10: 74LVC1G332; SOT-363_SC-70-6

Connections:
/AA_{13}: U8.29 (AA13), U9.26 (A13)
/AA_{14}: U8.28 (AA14), U9.1 (A14)
/AA_{15}: U8.27 (AA15)
/AA_{16}: U8.26 (AA16)
/A_{0}: P1.6 (A0), U7.45 (D15A-1), U9.10 (A0)
/A_{1}: P1.7 (A1), U7.25 (A0), U9.9 (A1)
/A_{2}: P1.8 (A2), U7.24 (A1), U9.8 (A2)
/A_{3}: P1.9 (A3), U7.23 (A2), U9.7 (A3)
/A_{4}: P1.10 (A4), U7.22 (A3), U9.6 (A4)
/A_{5}: P1.11 (A5), U7.21 (A4), U9.5 (A5)
/A_{6}: P1.12 (A6), U7.20 (A5), U9.4 (A6)
/A_{7}: P1.13 (A7), U7.19 (A6), U9.3 (A7)
/A_{8}: P1.14 (A8), U7.18 (A7), U9.25 (A8)
/A_{9}: P1.15 (A9), U7.8 (A8), U9.24 (A9)
/A_{10}: P1.16 (A10), U7.7 (A9), U9.21 (A10)
/A_{11}: P1.17 (A11), U7.6 (A10), U9.23 (A11)
/A_{12}: P1.18 (A12), U7.5 (A11), U8.32 (A12), U9.2 (A12)
/A_{13}: P1.19 (A13), U7.4 (A12), U8.1 (A13)
/A_{14}: P1.20 (A14), U8.2 (A14)
/A_{15}: P1.21 (A15), U7.26 (~CE), U8.3 (A15)
/CLK: P1.2 (CLK), U10.6
/D_{0}: P1.22 (D0), U7.29 (D0), U8.5 (D0), U9.11 (Q0)
/D_{1}: P1.23 (D1), U7.31 (D1), U8.6 (D1), U9.12 (Q1)
/D_{2}: P1.24 (D2), U7.33 (D2), U8.7 (D2), U9.13 (Q2)
/D_{3}: P1.25 (D3), U7.35 (D3), U8.8 (D3), U9.15 (Q3)
/D_{4}: P1.26 (D4), U7.38 (D4), U8.9 (D4), U9.16 (Q4)
/D_{5}: P1.27 (D5), U7.40 (D5), U8.10 (D5), U9.17 (Q5)
/D_{6}: P1.28 (D6), U7.42 (D6), U8.11 (D6), U9.18 (Q6)
/D_{7}: P1.29 (D7), U7.44 (D7), U8.12 (D7), U9.19 (Q7)
/RA_{14}: U7.3 (A13), U8.15 (RA14)
/RA_{15}: U7.2 (A14), U8.16 (RA15)
/RA_{16}: U7.1 (A15), U8.17 (RA16)
/RA_{17}: U7.48 (A16), U8.18 (RA17)
/RA_{18}: U7.17 (A17), U8.19 (RA18)
/RA_{19}: U7.16 (A18), U8.20 (RA19)
/RA_{20}: U7.9 (A19), U8.21 (RA20)
/RA_{21}: U8.22 (RA21)
/RA_{22}: U8.25 (RA22)
/~CS: P1.5 (~CS), U8.31 (~CS), U10.3
/~CS_{OR}: R17.1, U9.20 (~CS), U10.4
/~CS_{RAM}: U8.14 (~RAM_CS), U10.1
/~RD: P1.4 (~RD), U7.28 (~OE), U9.22 (~OE)
/~RST: P1.30 (~RST), U8.13 (~RESET)
/~WR: P1.3 (~WR), U7.11 (~WE), U8.30 (~WR), U9.27 (~WE)
GND: C19.2, C20.2, C21.2, C22.2, P1.32 (GND), U7.27 (GND), U7.46 (GND), U7.47 (~BYTE), U8.4 (GND4), U8.23 (GND23), U9.14 (GND), U10.2 (GND)
VCC: C19.1, C20.1, C21.1, C22.1, P1.1 (VCC), R17.2, U7.12 (~RP), U7.37 (VCC), U8.24 (VCC), U9.28 (VCC), U10.5 (VCC)

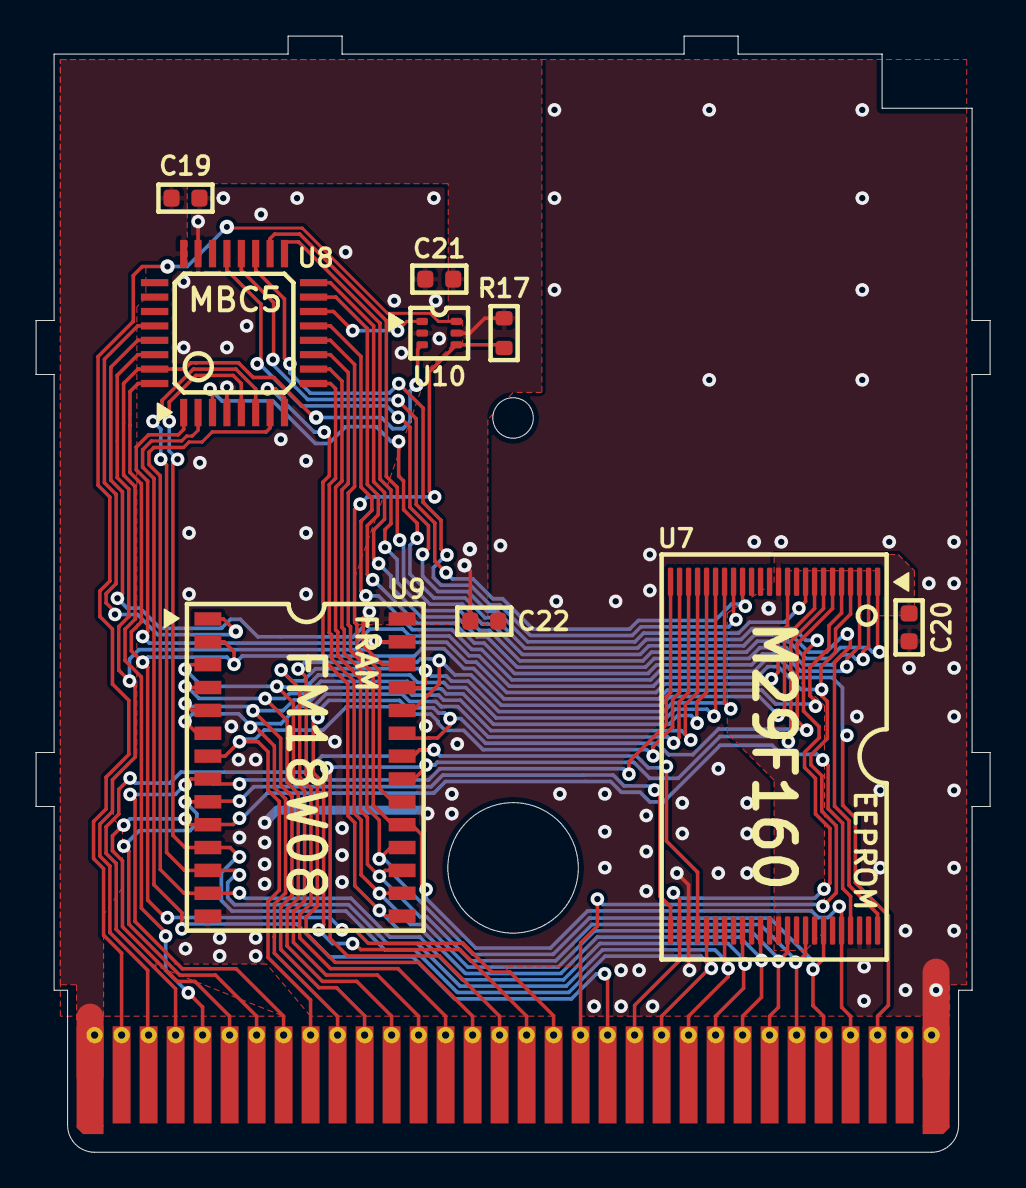
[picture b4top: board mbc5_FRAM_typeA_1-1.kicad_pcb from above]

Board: 2 copper layers, 53.0 x 62.0 mm, 10 parts (0 on the bottom side), 42 nets.
